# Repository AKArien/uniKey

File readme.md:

# Unikey

I think this name is corny as hell, but i needed one, sooo

Very unhappy with the way keyboards are currently handled (i’ll write my manifesto one day and i’ll link it here), this is my custom keyboard’s firmware, using the HID unicode page. It contains firmware source code and files i use to make the hardware, as well as examples to make your own.

# Hacking

If you want to change the layout for the unicode mode, check out src/key/unicode.h

If you want to tweak and re-use the usb reports, check out src/descriptors.h.

If you want a « classic » keyboard with one of the microcontrollers / physical builds (see below), you can change the code to force the mode and re-use it from there.

If you want a « classic » keyboard with another microncontroller / physical build, check out project [Golem](https://golem.hu/) and [QMK](https://github.com/qmk/qmk_firmware).

# Hardware

There is currently one physical keyboard in the project, though i do plan on making more.
The names used below are the ones needed for compilation of the firmware with them. Check firmware section for more details.

ALL_MAINBOARD :
- Physical configuration :
  - Ortholinear, 266\*95mm
  - Split, 2\*2,5-wide bottom-row keys « spacebar », 2-tall rightmost key « enter/return »
  - 5\*14,
- Available schematics use :
  - An arduino pro mini
  - 66 keys and as many diodes
  - Resistors and zener diodes for V-USB
- Features (almost) all the keys needed to make a classic keyboard, including « pinky keys » and arrow keys.
  - Lacks function keys, though you could probably easily add them to the topmost row (the keys that usually have numbers) with a modifier, or straight up adding a row of keys.
  - Doesn’t have space for both an escape and another key on the left of the topmost row (though most users probably wouldn’t even notice)
  - Assuming standard placement of return, backslash and modifiers, there is not really space for a classicly positioned « delete next » key. You could rather easily modify the pcb to make the « enter » key 1\*1, freeing space for another key and placing your deleting keys as you wish. The default is to have « delete previous » in the split long key on the bottom row and « delete next » in the top right corner.

# Firmware

The goal of the project is to make a keyboard that uses the Unicode HID page (0x10) for the host OS to use firmware-decided characters. In other words, a *really* plug and play keyboard.

As mentionned in hardware section, this repository will likely eventually have more keyboards. For now, only one exists.

Compilation of the firmware for the different models is scheduled to be handled with preprocessor flags passed to the makefile. So, to compile for the model ALL_MAINBOARD, you would use : ```make MODEL=ALL_MAINBOARD```

The ALL_MAINBOARD design uses the V-USB library, as it doesn’t have a dedicated USB chip.

To upload, use ```make upload ISP=<your in-circuit serial programmer, as per avrdude>```

Tip : UNOs can serve as in-cuircuit programmers ! They are named `arduino` to avrdude. Check out :
- Wiring and explanations : https://docs.arduino.cc/built-in-examples/arduino-isp/ArduinoISP/
- Arduino sketch : https://gist.github.com/srmq/0217a2844a9d82a6913ff989472a98dd

# Thanks

Obdev, for making V-USB

Sine Lab’s V-USB keyboard sample project, from which most of the code to use v-usb comes https://www.youtube.com/watch?v=6U_bHTnFu-g

The Kicad community, for making such good software and resources

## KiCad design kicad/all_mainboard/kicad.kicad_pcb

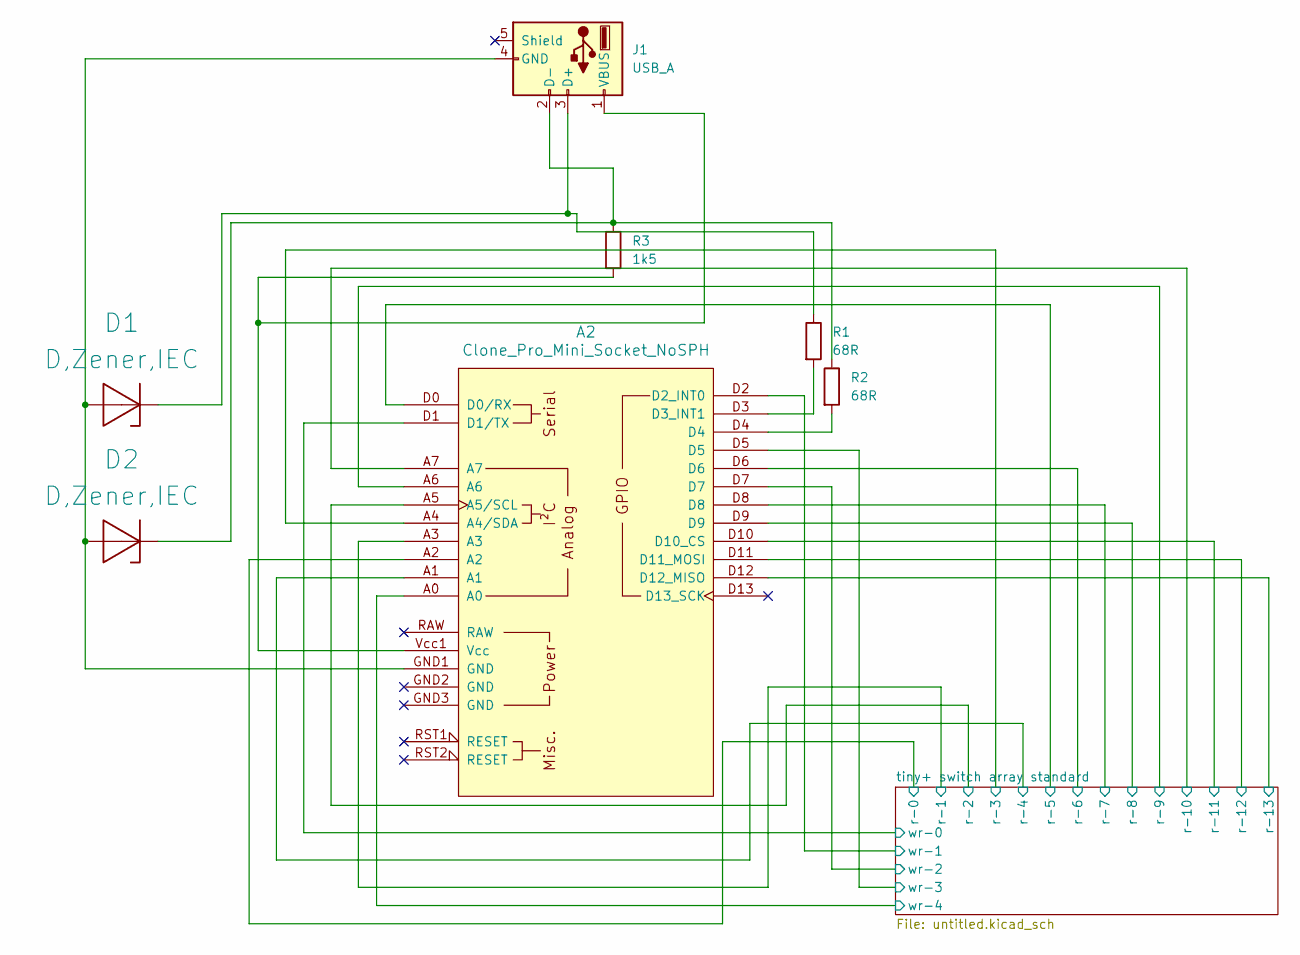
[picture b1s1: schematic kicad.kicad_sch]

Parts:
A2: Clone_Pro_Mini_Socket_NoSPH
D1, D2: D,Zener,IEC; D_DO-41_SOD81_P10.16mm_Horizontal
J1: USB_A; PinHeader_1x04_P2.00mm_Horizontal
R1, R2: 68R; D_DO-41_SOD81_P10.16mm_Horizontal
R3: 1k5; D_DO-41_SOD81_P10.16mm_Horizontal

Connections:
/tiny+ switch array standard/r-0: A2.A2; also elsewhere on the board
/tiny+ switch array standard/r-1: A2.A3; also elsewhere on the board
/tiny+ switch array standard/r-2: A2.A5 (A5/SCL); also elsewhere on the board
/tiny+ switch array standard/r-3: A2.A4 (A4/SDA); also elsewhere on the board
/tiny+ switch array standard/r-4: A2.A1; also elsewhere on the board
/tiny+ switch array standard/r-5: A2.D0 (D0/RX); also elsewhere on the board
/tiny+ switch array standard/r-6: A2.D6; also elsewhere on the board
/tiny+ switch array standard/r-7: A2.D8; also elsewhere on the board
/tiny+ switch array standard/r-8: A2.D9; also elsewhere on the board
/tiny+ switch array standard/r-9: A2.A6; also elsewhere on the board
/tiny+ switch array standard/r-10: A2.A7; also elsewhere on the board
/tiny+ switch array standard/r-11: A2.D10 (D10_CS); also elsewhere on the board
/tiny+ switch array standard/r-12: A2.D11 (D11_MOSI); also elsewhere on the board
/tiny+ switch array standard/r-13: A2.D12 (D12_MISO); also elsewhere on the board
/tiny+ switch array standard/wr-0: A2.D1 (D1/TX); also elsewhere on the board
/tiny+ switch array standard/wr-1: A2.D2 (D2_INT0); also elsewhere on the board
/tiny+ switch array standard/wr-2: A2.D7; also elsewhere on the board
/tiny+ switch array standard/wr-3: A2.D5; also elsewhere on the board
/tiny+ switch array standard/wr-4: A2.A0; also elsewhere on the board
unnamed: A2.D3 (D3_INT1), R1.2
unnamed: A2.D4, R2.2
unnamed: A2.Vcc1 (Vcc), J1.1 (VBUS), R3.2
unnamed: A2.GND1 (GND), D1.2 (A+), D2.2 (A+), J1.4 (GND)
unnamed: D1.1 (K-), J1.3 (D+), R1.1
unnamed: D2.1 (K-), J1.2 (D-), R2.1, R3.1

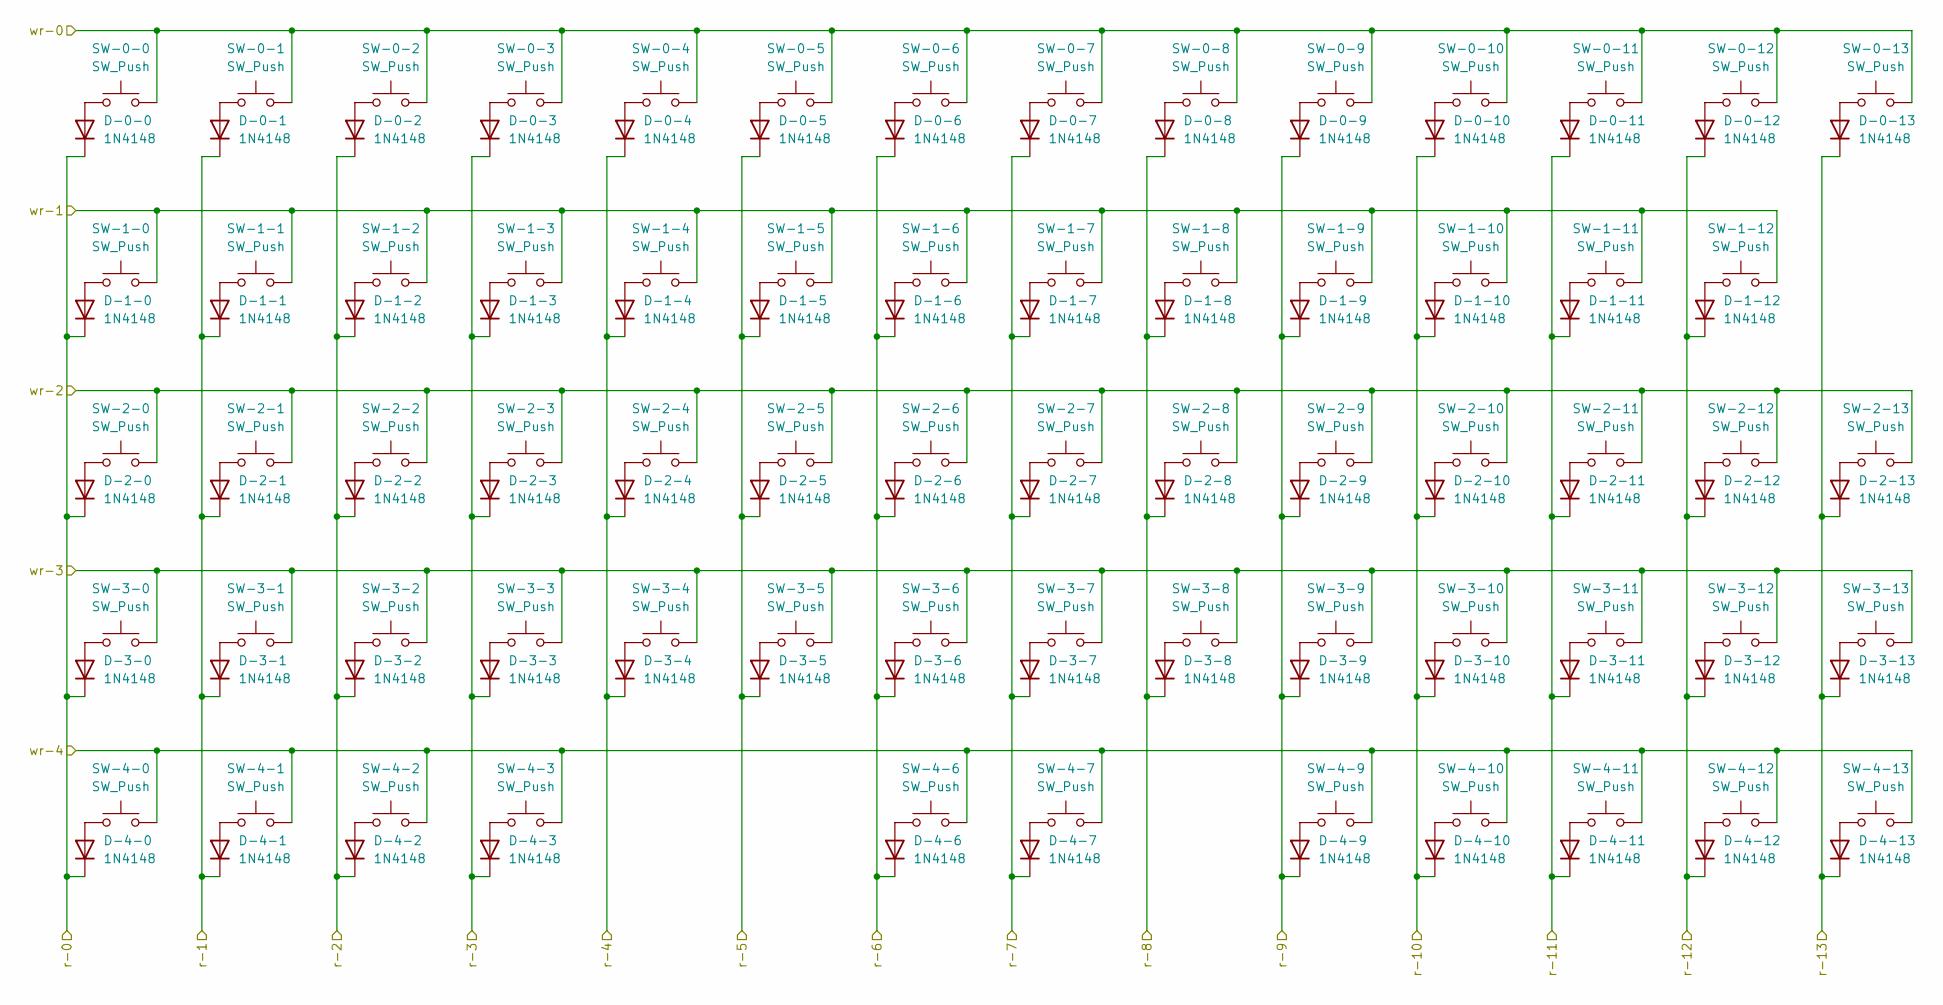
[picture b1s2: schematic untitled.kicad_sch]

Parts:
D-0-0, D-0-1, D-0-2, D-0-3, D-0-4, D-0-5, D-0-6, D-0-7, D-0-8, D-0-9, D-0-10, D-0-11, D-0-12, D-0-13, D-1-0, D-1-1, D-1-2, D-1-3, D-1-4, D-1-5, D-1-6, D-1-7, D-1-8, D-1-9, D-1-10, D-1-11, D-1-12, D-2-0, D-2-1, D-2-2, D-2-3, D-2-4, D-2-5, D-2-6, D-2-7, D-2-8, D-2-9, D-2-10, D-2-11, D-2-12, D-2-13, D-3-0, D-3-1, D-3-2, D-3-3, D-3-4, D-3-5, D-3-6, D-3-7, D-3-8, D-3-9, D-3-10, D-3-11, D-3-12, D-3-13, D-4-0, D-4-1, D-4-2, D-4-3, D-4-6, D-4-7, D-4-9, D-4-10, D-4-11, D-4-12, D-4-13: 1N4148; D_DO-35_SOD27_P7.62mm_Horizontal
SW-0-0, SW-0-1, SW-0-2, SW-0-3, SW-0-4, SW-0-5, SW-0-6, SW-0-7, SW-0-8, SW-0-9, SW-0-10, SW-0-11, SW-0-12, SW-0-13, SW-1-0, SW-1-1, SW-1-2, SW-1-3, SW-1-4, SW-1-5, SW-1-6, SW-1-7, SW-1-8, SW-1-9, SW-1-10, SW-1-11, SW-1-12, SW-2-0, SW-2-1, SW-2-2, SW-2-3, SW-2-4, SW-2-5, SW-2-6, SW-2-7, SW-2-8, SW-2-9, SW-2-10, SW-2-11, SW-2-12, SW-2-13, SW-3-0, SW-3-1, SW-3-2, SW-3-3, SW-3-4, SW-3-5, SW-3-6, SW-3-7, SW-3-8, SW-3-9, SW-3-10, SW-3-11, SW-3-12, SW-3-13, SW-4-0, SW-4-1, SW-4-2, SW-4-3, SW-4-6, SW-4-7, SW-4-9, SW-4-10, SW-4-11, SW-4-12, SW-4-13: SW_Push; SW_Cherry_MX_1.00u_PCB

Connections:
/tiny+ switch array standard/r-0: D-0-0.1 (K), D-1-0.1 (K), D-2-0.1 (K), D-3-0.1 (K), D-4-0.1 (K); also elsewhere on the board
/tiny+ switch array standard/r-1: D-0-1.1 (K), D-1-1.1 (K), D-2-1.1 (K), D-3-1.1 (K), D-4-1.1 (K); also elsewhere on the board
/tiny+ switch array standard/r-2: D-0-2.1 (K), D-1-2.1 (K), D-2-2.1 (K), D-3-2.1 (K), D-4-2.1 (K); also elsewhere on the board
/tiny+ switch array standard/r-3: D-0-3.1 (K), D-1-3.1 (K), D-2-3.1 (K), D-3-3.1 (K), D-4-3.1 (K); also elsewhere on the board
/tiny+ switch array standard/r-4: D-0-4.1 (K), D-1-4.1 (K), D-2-4.1 (K), D-3-4.1 (K); also elsewhere on the board
/tiny+ switch array standard/r-5: D-0-5.1 (K), D-1-5.1 (K), D-2-5.1 (K), D-3-5.1 (K); also elsewhere on the board
/tiny+ switch array standard/r-6: D-0-6.1 (K), D-1-6.1 (K), D-2-6.1 (K), D-3-6.1 (K), D-4-6.1 (K); also elsewhere on the board
/tiny+ switch array standard/r-7: D-0-7.1 (K), D-1-7.1 (K), D-2-7.1 (K), D-3-7.1 (K), D-4-7.1 (K); also elsewhere on the board
/tiny+ switch array standard/r-8: D-0-8.1 (K), D-1-8.1 (K), D-2-8.1 (K), D-3-8.1 (K); also elsewhere on the board
/tiny+ switch array standard/r-9: D-0-9.1 (K), D-1-9.1 (K), D-2-9.1 (K), D-3-9.1 (K), D-4-9.1 (K); also elsewhere on the board
/tiny+ switch array standard/r-10: D-0-10.1 (K), D-1-10.1 (K), D-2-10.1 (K), D-3-10.1 (K), D-4-10.1 (K); also elsewhere on the board
/tiny+ switch array standard/r-11: D-0-11.1 (K), D-1-11.1 (K), D-2-11.1 (K), D-3-11.1 (K), D-4-11.1 (K); also elsewhere on the board
/tiny+ switch array standard/r-12: D-0-12.1 (K), D-1-12.1 (K), D-2-12.1 (K), D-3-12.1 (K), D-4-12.1 (K); also elsewhere on the board
/tiny+ switch array standard/r-13: D-0-13.1 (K), D-2-13.1 (K), D-3-13.1 (K), D-4-13.1 (K); also elsewhere on the board
/tiny+ switch array standard/wr-0: SW-0-0.2, SW-0-1.2, SW-0-2.2, SW-0-3.2, SW-0-4.2, SW-0-5.2, SW-0-6.2, SW-0-7.2, SW-0-8.2, SW-0-9.2, SW-0-10.2, SW-0-11.2, SW-0-12.2, SW-0-13.2; also elsewhere on the board
/tiny+ switch array standard/wr-1: SW-1-0.2, SW-1-1.2, SW-1-2.2, SW-1-3.2, SW-1-4.2, SW-1-5.2, SW-1-6.2, SW-1-7.2, SW-1-8.2, SW-1-9.2, SW-1-10.2, SW-1-11.2, SW-1-12.2; also elsewhere on the board
/tiny+ switch array standard/wr-2: SW-2-0.2, SW-2-1.2, SW-2-2.2, SW-2-3.2, SW-2-4.2, SW-2-5.2, SW-2-6.2, SW-2-7.2, SW-2-8.2, SW-2-9.2, SW-2-10.2, SW-2-11.2, SW-2-12.2, SW-2-13.2; also elsewhere on the board
/tiny+ switch array standard/wr-3: SW-3-0.2, SW-3-1.2, SW-3-2.2, SW-3-3.2, SW-3-4.2, SW-3-5.2, SW-3-6.2, SW-3-7.2, SW-3-8.2, SW-3-9.2, SW-3-10.2, SW-3-11.2, SW-3-12.2, SW-3-13.2; also elsewhere on the board
/tiny+ switch array standard/wr-4: SW-4-0.2, SW-4-1.2, SW-4-2.2, SW-4-3.2, SW-4-6.2, SW-4-7.2, SW-4-9.2, SW-4-10.2, SW-4-11.2, SW-4-12.2, SW-4-13.2; also elsewhere on the board
unnamed: D-0-0.2 (A), SW-0-0.1
unnamed: D-0-1.2 (A), SW-0-1.1
unnamed: D-0-2.2 (A), SW-0-2.1
unnamed: D-0-3.2 (A), SW-0-3.1
unnamed: D-0-4.2 (A), SW-0-4.1
unnamed: D-0-5.2 (A), SW-0-5.1
unnamed: D-0-6.2 (A), SW-0-6.1
unnamed: D-0-7.2 (A), SW-0-7.1
unnamed: D-0-8.2 (A), SW-0-8.1
unnamed: D-0-9.2 (A), SW-0-9.1
unnamed: D-0-10.2 (A), SW-0-10.1
unnamed: D-0-11.2 (A), SW-0-11.1
unnamed: D-0-12.2 (A), SW-0-12.1
unnamed: D-0-13.2 (A), SW-0-13.1
unnamed: D-1-0.2 (A), SW-1-0.1
unnamed: D-1-1.2 (A), SW-1-1.1
unnamed: D-1-2.2 (A), SW-1-2.1
unnamed: D-1-3.2 (A), SW-1-3.1
unnamed: D-1-4.2 (A), SW-1-4.1
unnamed: D-1-5.2 (A), SW-1-5.1
unnamed: D-1-6.2 (A), SW-1-6.1
unnamed: D-1-7.2 (A), SW-1-7.1
unnamed: D-1-8.2 (A), SW-1-8.1
unnamed: D-1-9.2 (A), SW-1-9.1
unnamed: D-1-10.2 (A), SW-1-10.1
unnamed: D-1-11.2 (A), SW-1-11.1
unnamed: D-1-12.2 (A), SW-1-12.1
unnamed: D-2-0.2 (A), SW-2-0.1
unnamed: D-2-1.2 (A), SW-2-1.1
unnamed: D-2-2.2 (A), SW-2-2.1
unnamed: D-2-3.2 (A), SW-2-3.1
unnamed: D-2-4.2 (A), SW-2-4.1
unnamed: D-2-5.2 (A), SW-2-5.1
unnamed: D-2-6.2 (A), SW-2-6.1
unnamed: D-2-7.2 (A), SW-2-7.1
unnamed: D-2-8.2 (A), SW-2-8.1
unnamed: D-2-9.2 (A), SW-2-9.1
unnamed: D-2-10.2 (A), SW-2-10.1
unnamed: D-2-11.2 (A), SW-2-11.1
unnamed: D-2-12.2 (A), SW-2-12.1
unnamed: D-2-13.2 (A), SW-2-13.1
unnamed: D-3-0.2 (A), SW-3-0.1
unnamed: D-3-1.2 (A), SW-3-1.1
unnamed: D-3-2.2 (A), SW-3-2.1
unnamed: D-3-3.2 (A), SW-3-3.1
unnamed: D-3-4.2 (A), SW-3-4.1
unnamed: D-3-5.2 (A), SW-3-5.1
unnamed: D-3-6.2 (A), SW-3-6.1
unnamed: D-3-7.2 (A), SW-3-7.1
unnamed: D-3-8.2 (A), SW-3-8.1
unnamed: D-3-9.2 (A), SW-3-9.1
unnamed: D-3-10.2 (A), SW-3-10.1
unnamed: D-3-11.2 (A), SW-3-11.1
unnamed: D-3-12.2 (A), SW-3-12.1
unnamed: D-3-13.2 (A), SW-3-13.1
unnamed: D-4-0.2 (A), SW-4-0.1
unnamed: D-4-1.2 (A), SW-4-1.1
unnamed: D-4-2.2 (A), SW-4-2.1
unnamed: D-4-3.2 (A), SW-4-3.1
unnamed: D-4-6.2 (A), SW-4-6.1
unnamed: D-4-7.2 (A), SW-4-7.1
unnamed: D-4-9.2 (A), SW-4-9.1
unnamed: D-4-10.2 (A), SW-4-10.1
unnamed: D-4-11.2 (A), SW-4-11.1
unnamed: D-4-12.2 (A), SW-4-12.1
unnamed: D-4-13.2 (A), SW-4-13.1

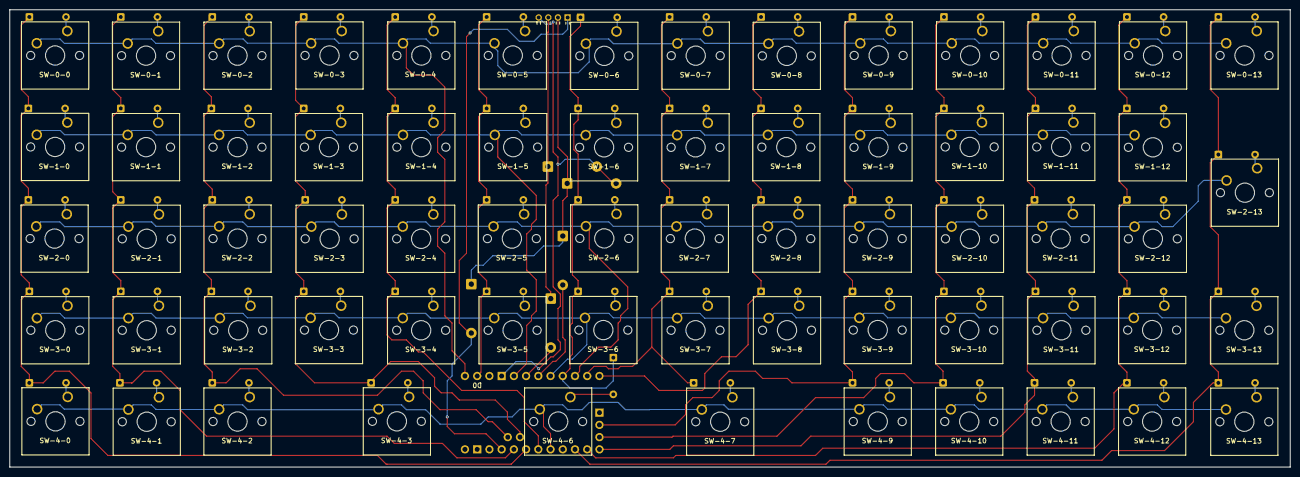
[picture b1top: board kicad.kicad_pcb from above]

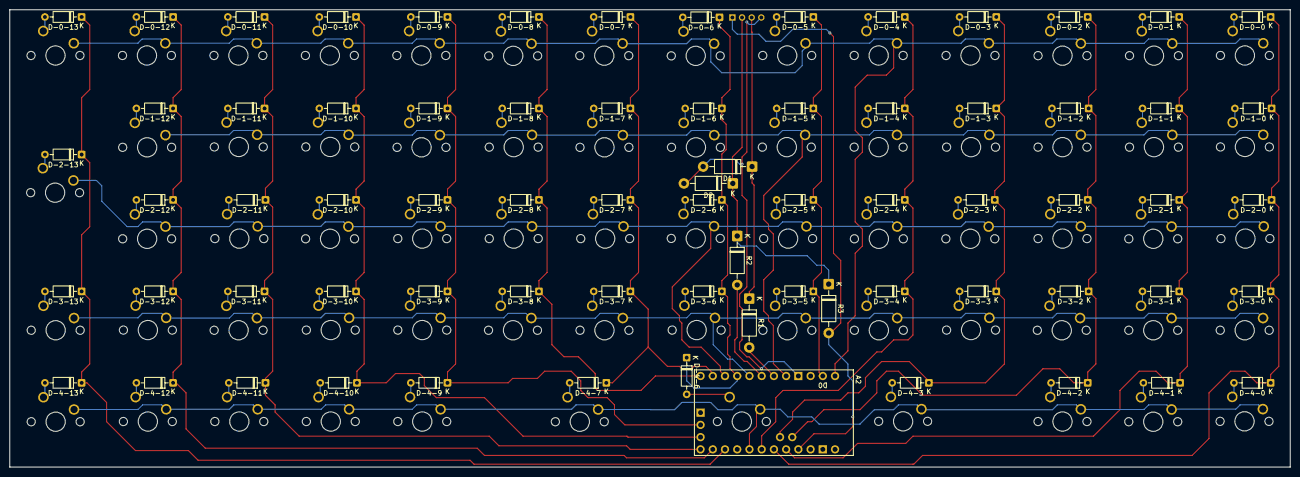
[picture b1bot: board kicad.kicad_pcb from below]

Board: 2 copper layers, 266.0 x 95.0 mm, 139 parts (72 on the bottom side), 91 nets.

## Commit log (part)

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2025-05-09 initial commit : rough skeleton
2025-07-29 rough draft of sequence
2025-08-16 one less compilation error
2025-08-18 add firmware to gitignore
2025-08-18 fixed typo
2025-08-18 fixed typo honestly i should do a 1984 because i don’t like where this is going
2025-08-19 remove old comments, some more hacking to test stuff
2025-08-19 changed the way we handle changing between modes
2025-08-19 a few more unicode codes
2025-08-19 fixed up some keys, codes and layouts
2025-08-21 clean schema with dirty pcb i probably should rewire everything would save 3 meters of copper wire
2025-08-23 the project is now made for many keyboards models, with some additional fuckery required for it
2025-08-24 added pins.h file for each keyboard, defines which pins fill which role
2025-08-24 updated (implemented lol) logic for getting which keys are currently pressed
2025-08-24 pins writes should be good if i didn’t logic too poorly ?
2025-08-24 comments update
2025-08-24 does that work ? now writing to report buffer
2025-08-24 fixed errors and typos
2025-08-24 corrected pins definitions and initialisation
2025-08-26 added kicad files
2025-08-26 added fdel keycode and edited layout for all_mainboard
2025-08-26 updated Makefile to comply with new readme
2025-08-26 mention isp in readme
2025-08-27 updated model selection to makefile defintions
2025-08-27 fixed bad makefile
2025-08-27 whatever
2025-08-27 add -Wall to makefile, typos in main
2025-08-27 i changed my mind
2025-09-20 slight update to pcb to cross at 90 degrees
2025-09-20 update readme as i cannot markdown
2025-09-20 fixed update_key_buffer_x functions
2025-09-20 cleanups
2025-09-21 license
2025-09-24 clarified things in readme
2025-10-05 minor pcb and schema updates
2025-10-05 (probably) final revision of all_mainboard pcb
2025-10-12 renamed key.h to hid-kb-keys.h
2025-10-12 clear up hacking in readme
2025-12-07 active layer
2025-12-07 update naming
2025-12-07 revamp layouts file and add unicode codes
2026-01-19 deleted ill-included usbdrv from vusb
2026-05-23 spaces -> tabs
